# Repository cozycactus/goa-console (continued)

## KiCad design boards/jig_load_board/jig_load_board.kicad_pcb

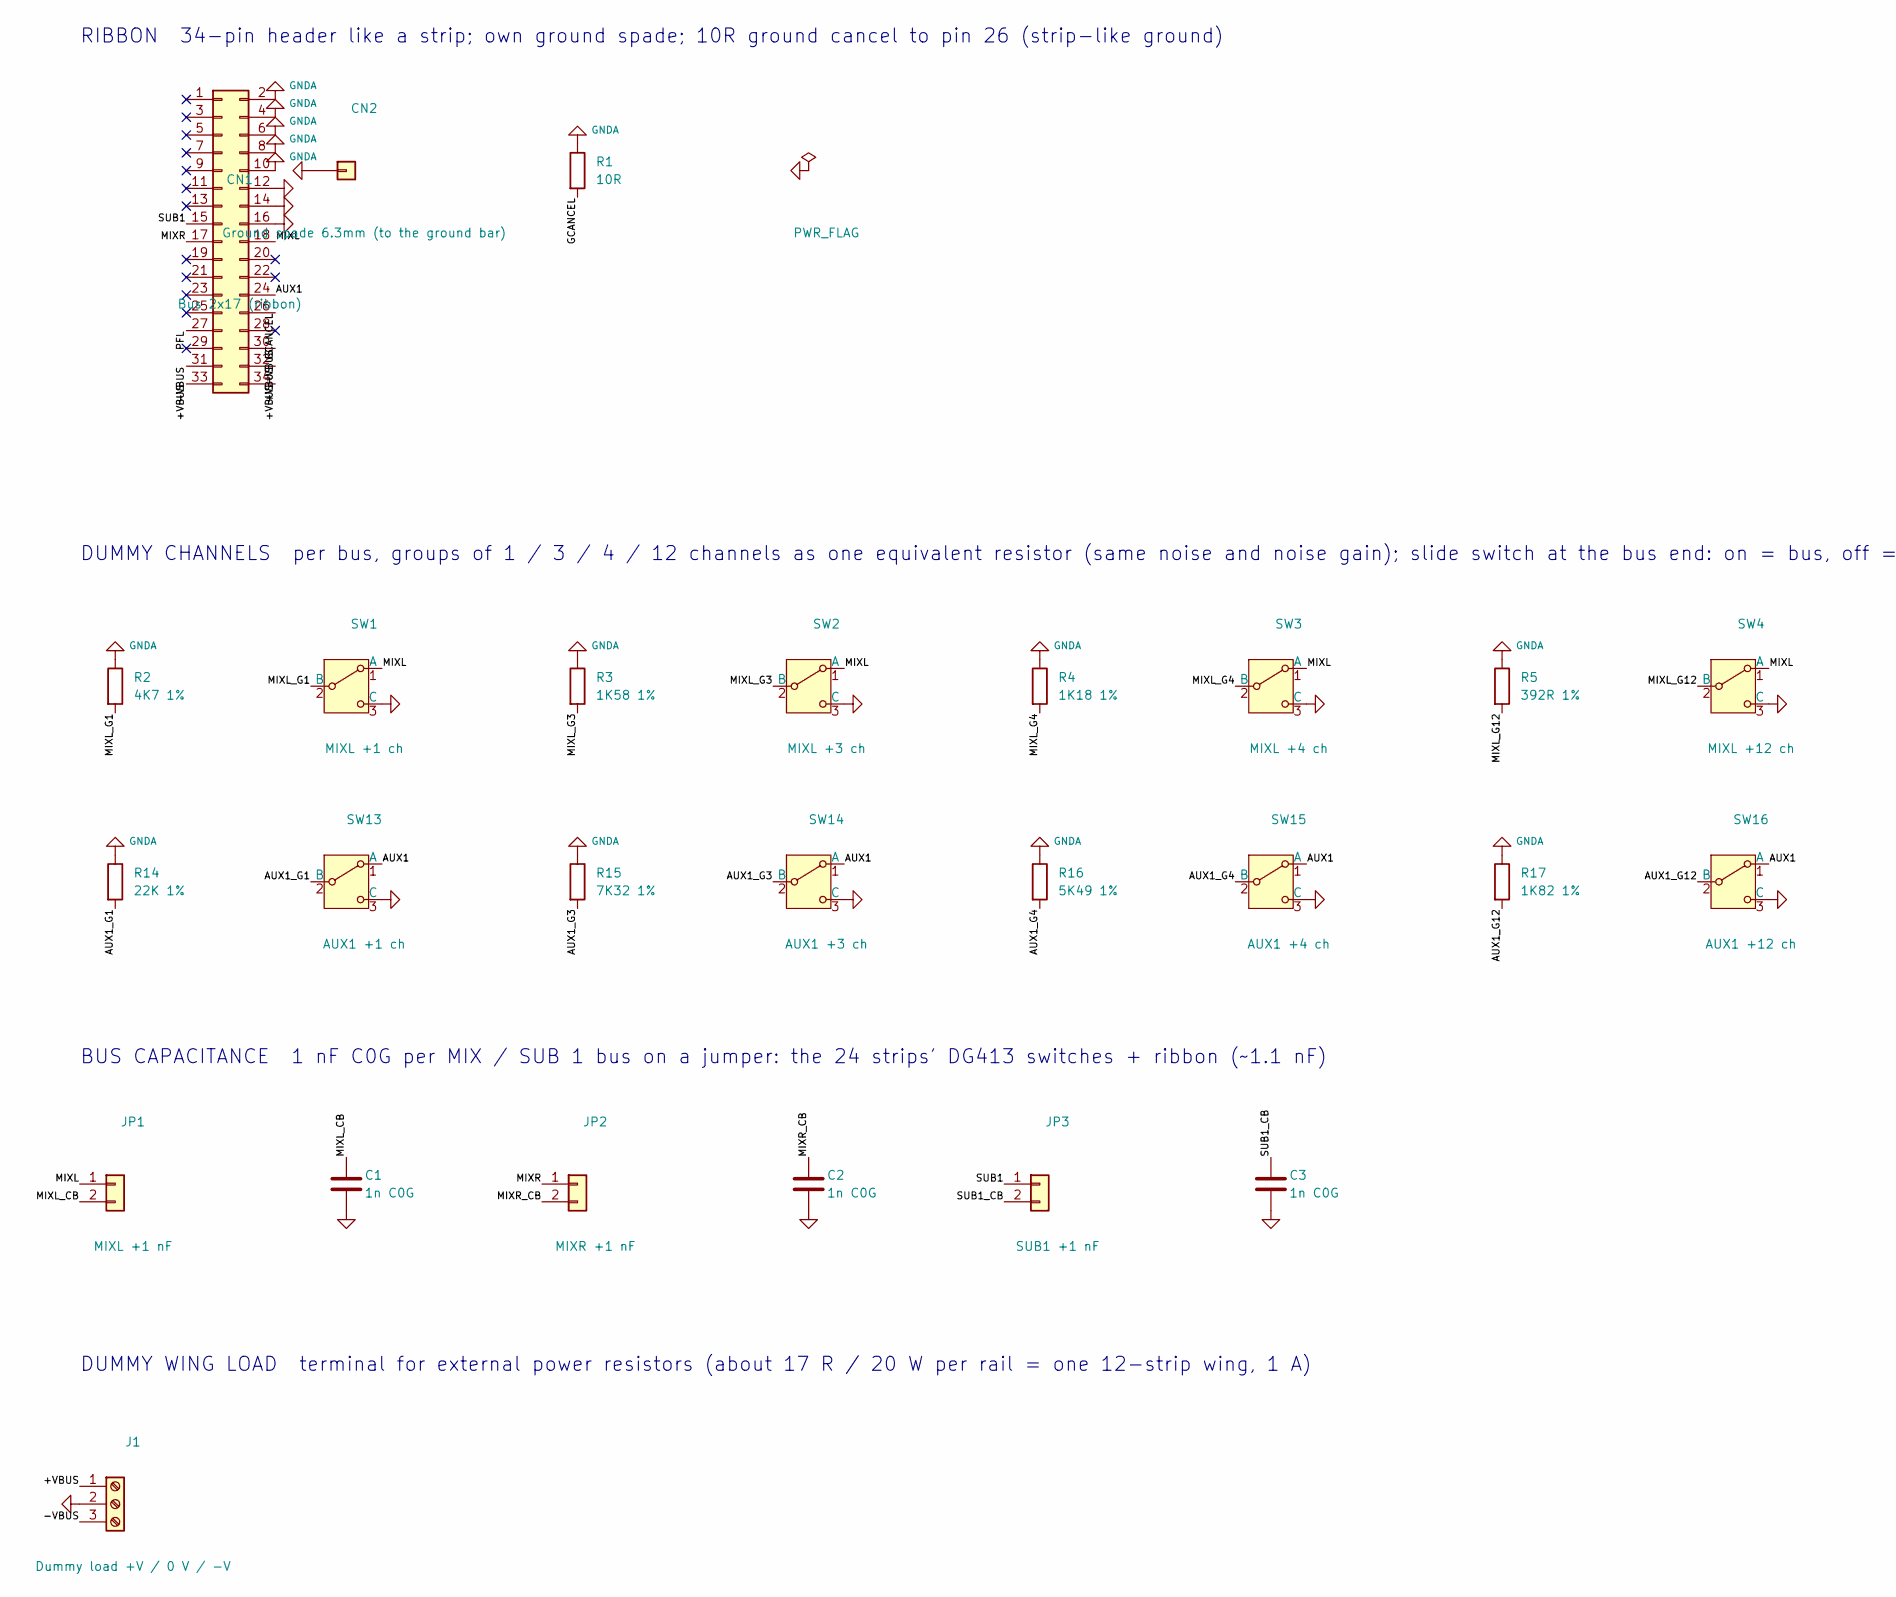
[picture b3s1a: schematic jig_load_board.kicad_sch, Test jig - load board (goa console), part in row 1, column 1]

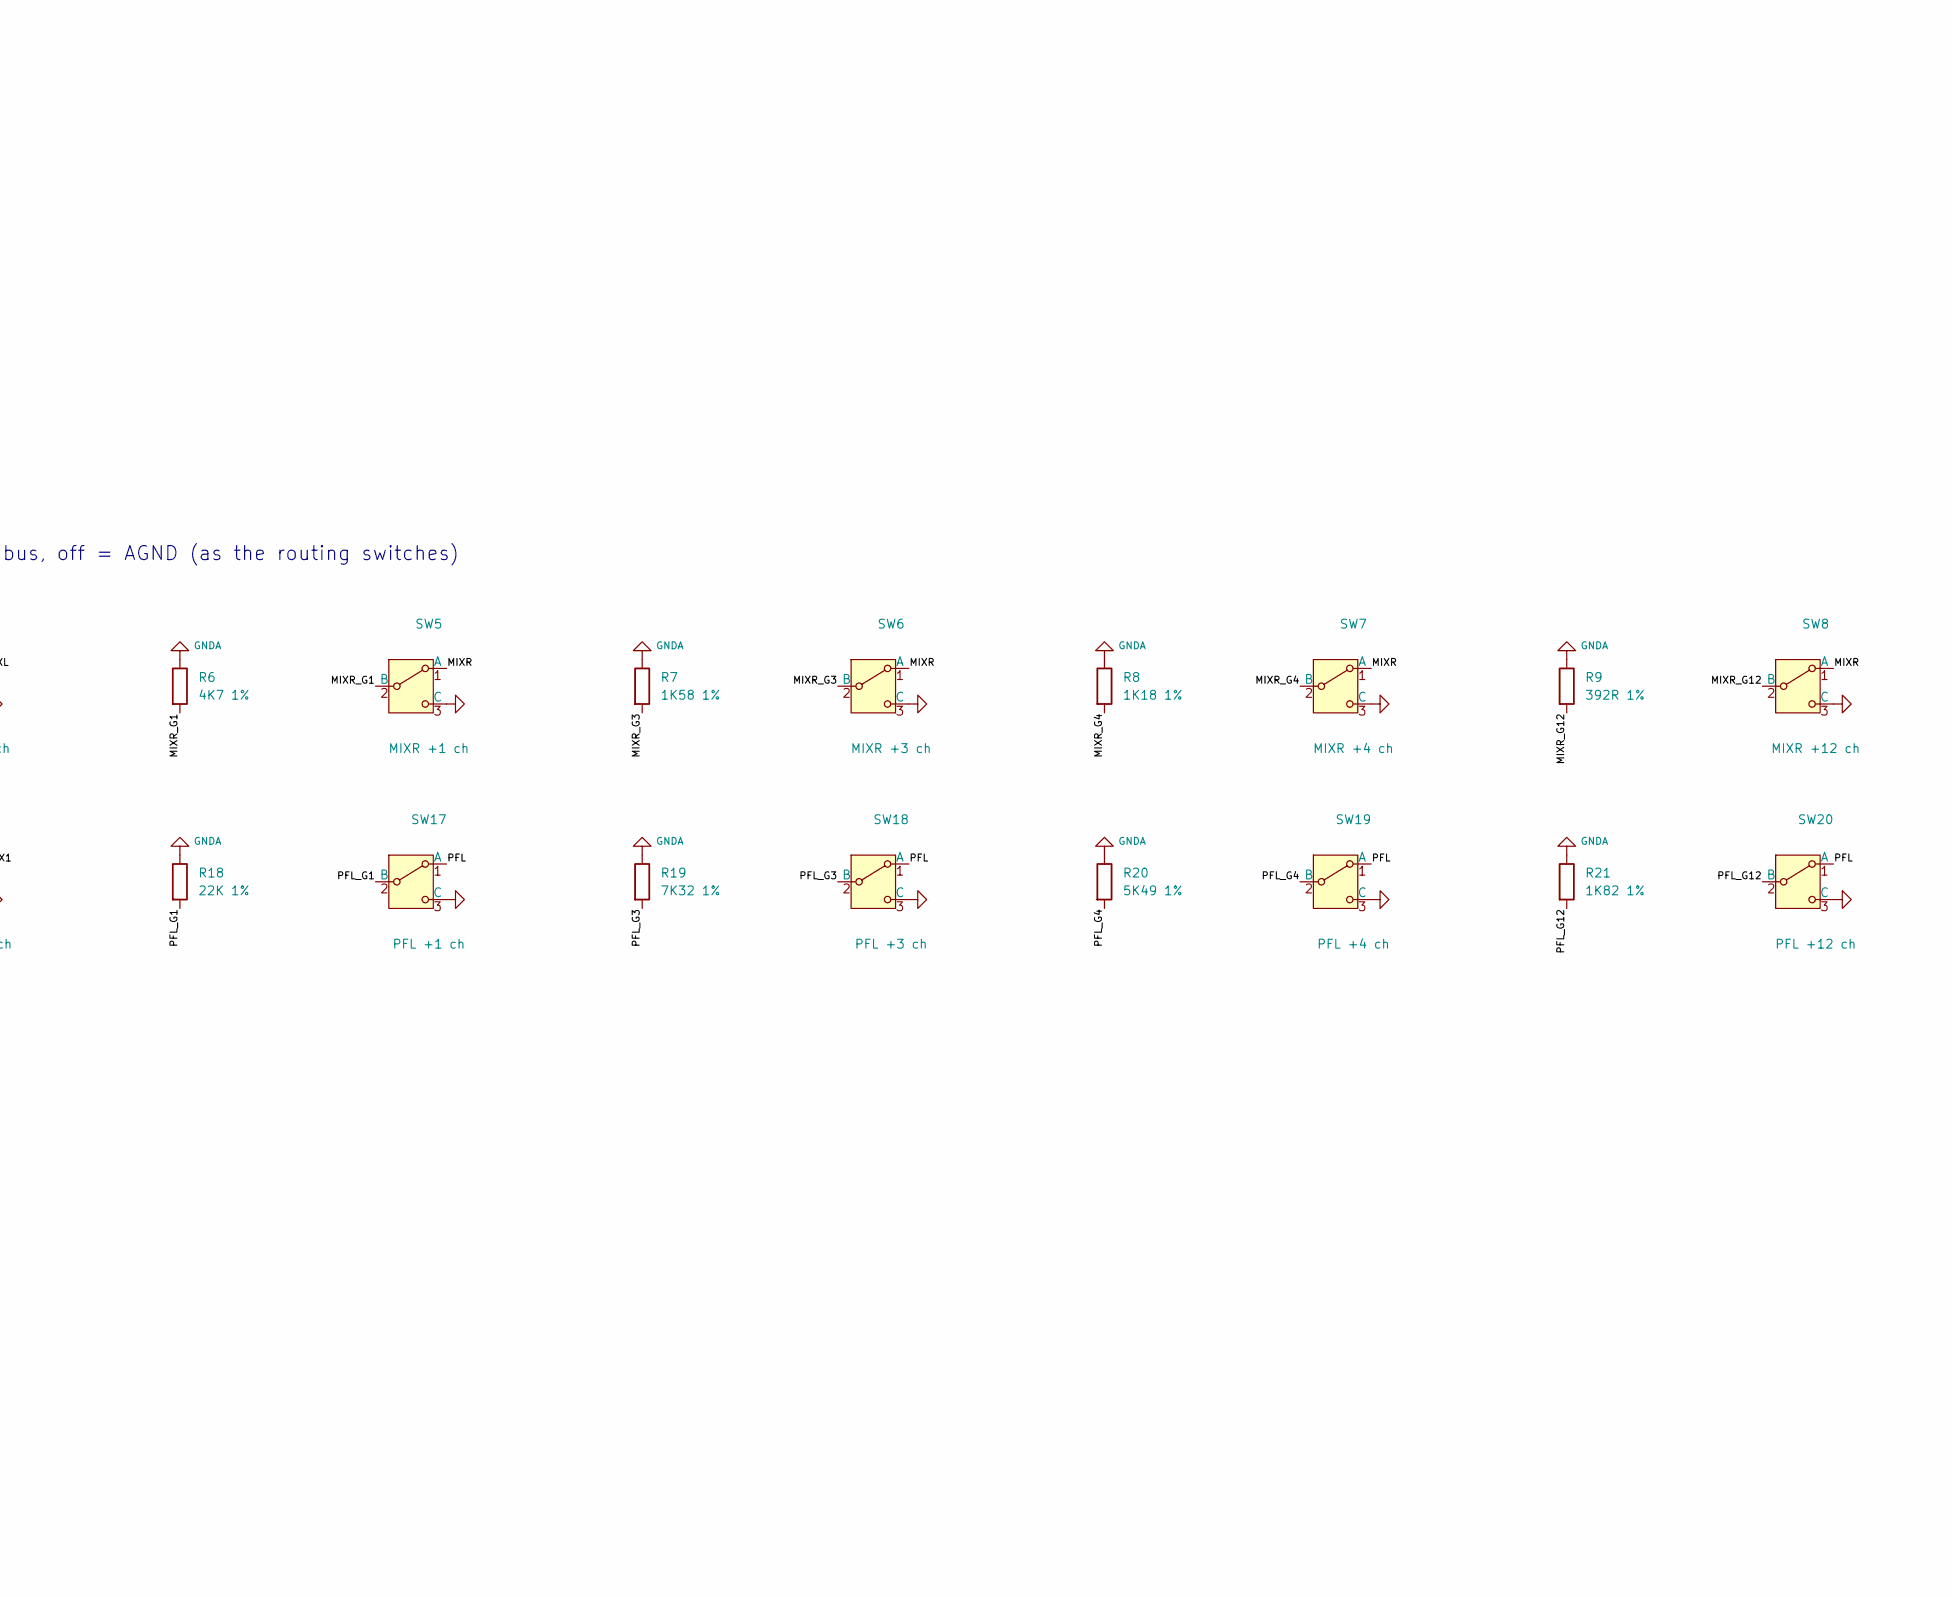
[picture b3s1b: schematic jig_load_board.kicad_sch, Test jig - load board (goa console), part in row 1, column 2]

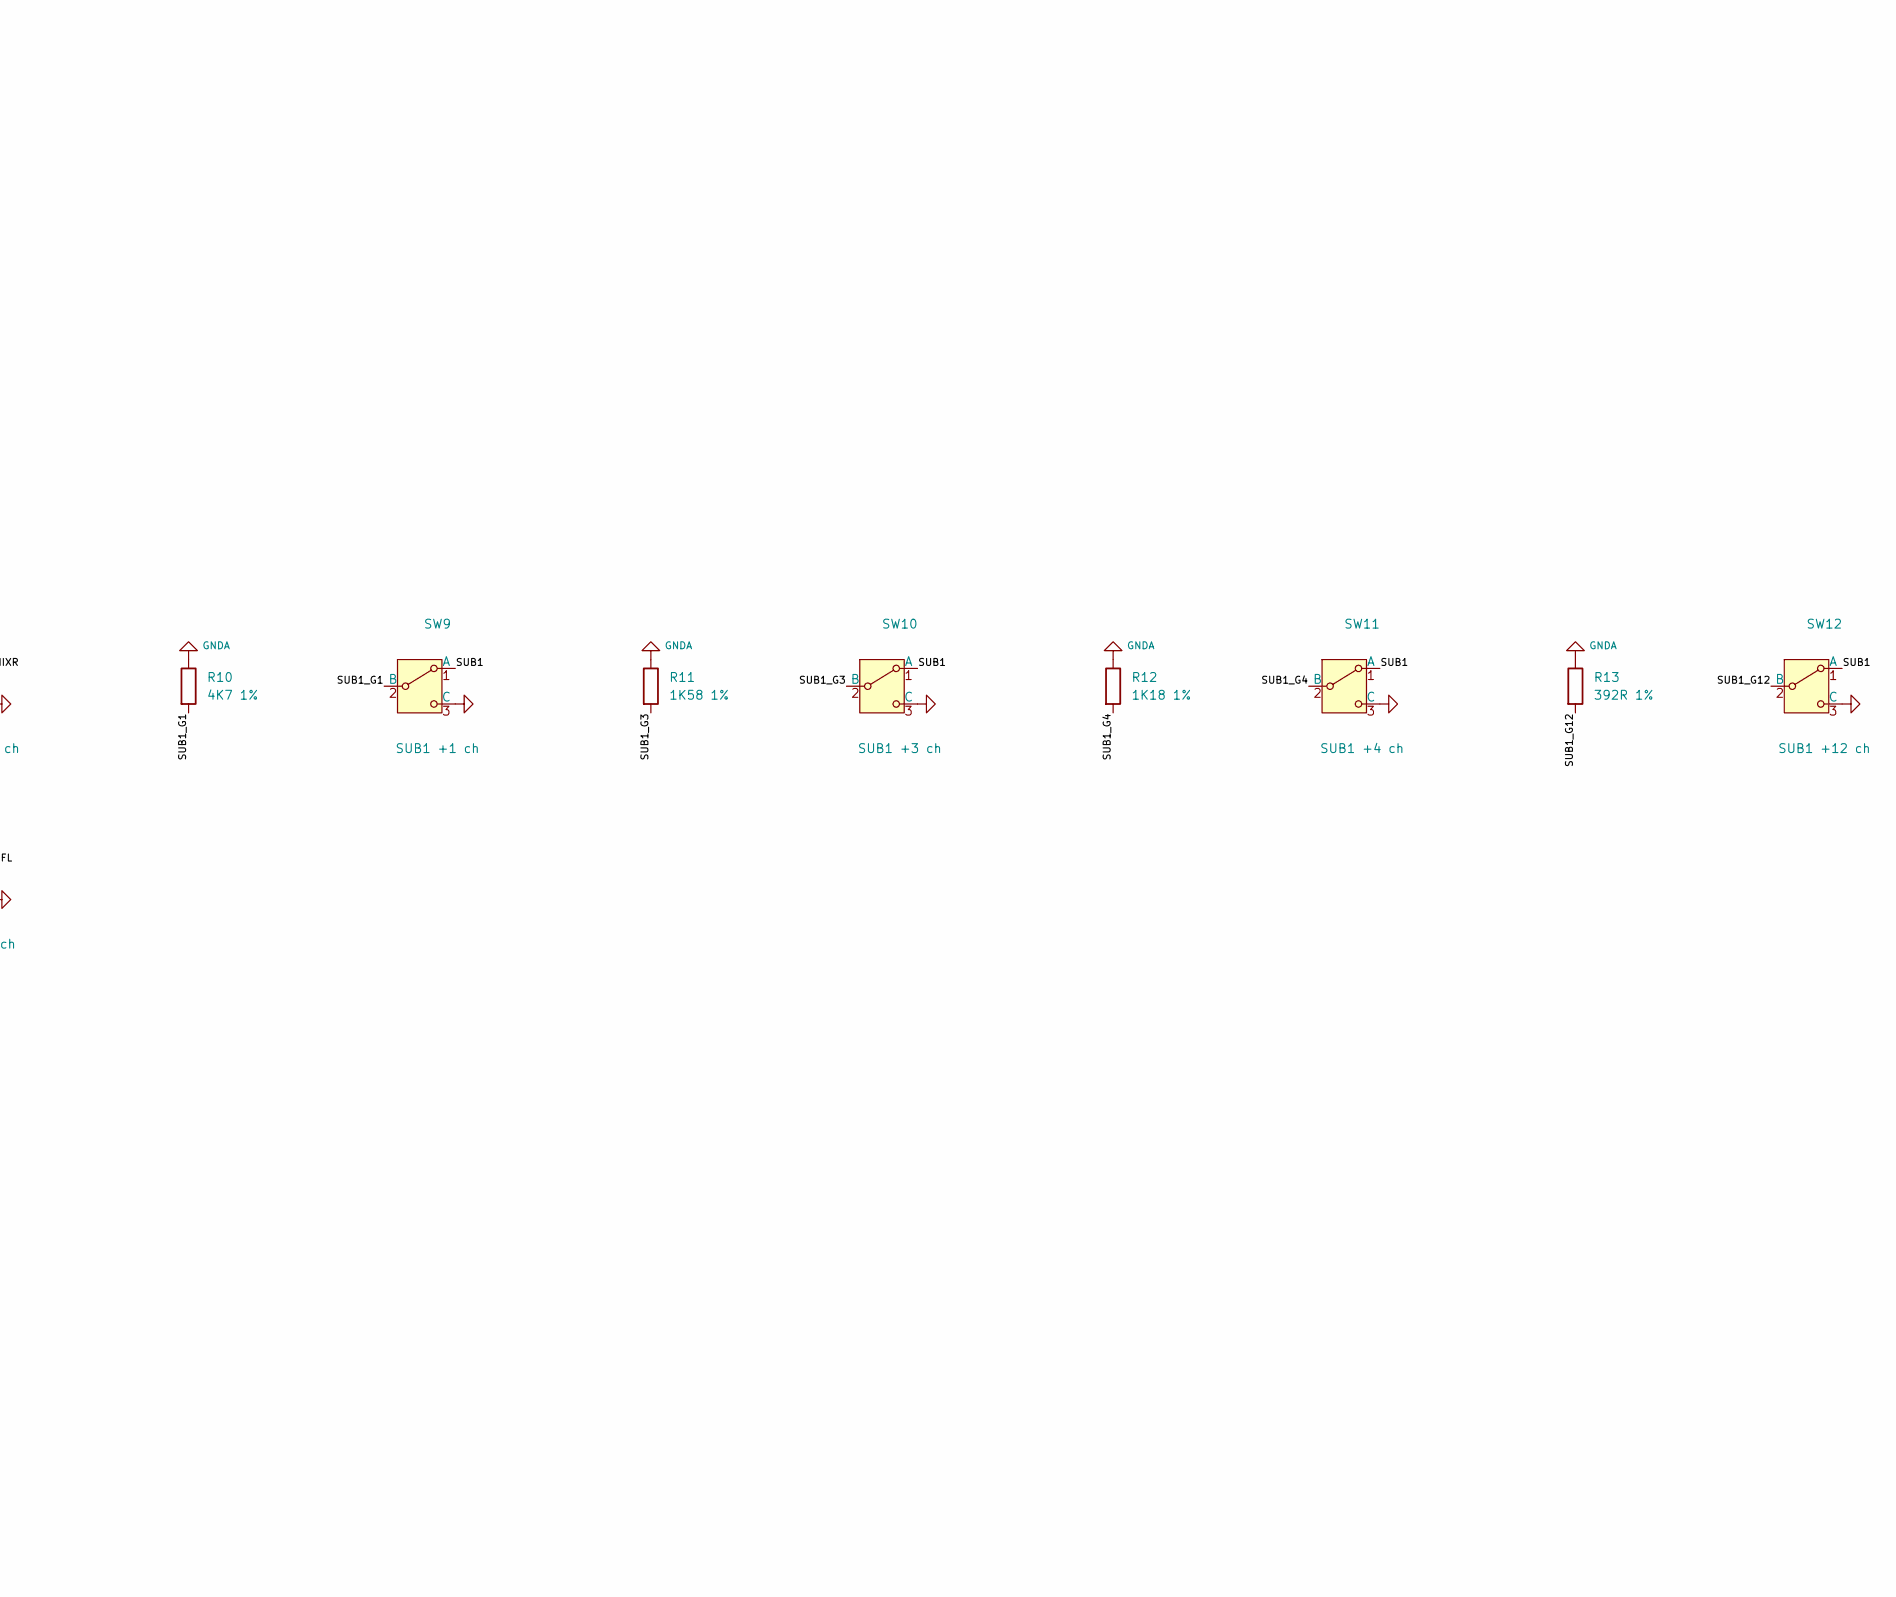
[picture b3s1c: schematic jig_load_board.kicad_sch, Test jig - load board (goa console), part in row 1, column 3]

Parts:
C1, C2, C3: 1n C0G; C_0805_2012Metric; MPN KEMET C0805C102J5GACTU
CN1: Bus 2x17 (ribbon); IDC-Header_2x17_P2.54mm_Vertical; MPN Wurth 61203421621 (2x17 box header)
CN2: Ground spade 6.3mm (to the ground bar); Keystone_1287-ST_FastOn_Tab_6.35mm; MPN Keystone 1287-ST
J1: Dummy load +V / 0 V / -V; TerminalBlock_Phoenix_MKDS-1,5-3-5.08_1x03_P5.08mm_Horizont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; MPN Phoenix 1715734 MKDS 1,5/3-5,08
JP1: MIXL +1 nF; PinHeader_1x02_P2.54mm_Vertical; MPN 2.54 mm header + shunt
JP2: MIXR +1 nF; PinHeader_1x02_P2.54mm_Vertical; MPN 2.54 mm header + shunt
JP3: SUB1 +1 nF; PinHeader_1x02_P2.54mm_Vertical; MPN 2.54 mm header + shunt
R1: 10R; R_0805_2012Metric
R2, R6, R10: 4K7 1%; R_0805_2012Metric
R3, R7, R11: 1K58 1%; R_0805_2012Metric
R4, R8, R12: 1K18 1%; R_0805_2012Metric
R5, R9, R13: 392R 1%; R_0805_2012Metric
R14, R18: 22K 1%; R_0805_2012Metric
R15, R19: 7K32 1%; R_0805_2012Metric
R16, R20: 5K49 1%; R_0805_2012Metric
R17, R21: 1K82 1%; R_0805_2012Metric
SW1: MIXL +1 ch; SW_Slide_SPDT_Straight_CK_OS102011MS2Q; MPN C&K OS102011MS2QN1
SW2: MIXL +3 ch; SW_Slide_SPDT_Straight_CK_OS102011MS2Q; MPN C&K OS102011MS2QN1
SW3: MIXL +4 ch; SW_Slide_SPDT_Straight_CK_OS102011MS2Q; MPN C&K OS102011MS2QN1
SW4: MIXL +12 ch; SW_Slide_SPDT_Straight_CK_OS102011MS2Q; MPN C&K OS102011MS2QN1
SW5: MIXR +1 ch; SW_Slide_SPDT_Straight_CK_OS102011MS2Q; MPN C&K OS102011MS2QN1
SW6: MIXR +3 ch; SW_Slide_SPDT_Straight_CK_OS102011MS2Q; MPN C&K OS102011MS2QN1
SW7: MIXR +4 ch; SW_Slide_SPDT_Straight_CK_OS102011MS2Q; MPN C&K OS102011MS2QN1
SW8: MIXR +12 ch; SW_Slide_SPDT_Straight_CK_OS102011MS2Q; MPN C&K OS102011MS2QN1
SW9: SUB1 +1 ch; SW_Slide_SPDT_Straight_CK_OS102011MS2Q; MPN C&K OS102011MS2QN1
SW10: SUB1 +3 ch; SW_Slide_SPDT_Straight_CK_OS102011MS2Q; MPN C&K OS102011MS2QN1
SW11: SUB1 +4 ch; SW_Slide_SPDT_Straight_CK_OS102011MS2Q; MPN C&K OS102011MS2QN1
SW12: SUB1 +12 ch; SW_Slide_SPDT_Straight_CK_OS102011MS2Q; MPN C&K OS102011MS2QN1
SW13: AUX1 +1 ch; SW_Slide_SPDT_Straight_CK_OS102011MS2Q; MPN C&K OS102011MS2QN1
SW14: AUX1 +3 ch; SW_Slide_SPDT_Straight_CK_OS102011MS2Q; MPN C&K OS102011MS2QN1
SW15: AUX1 +4 ch; SW_Slide_SPDT_Straight_CK_OS102011MS2Q; MPN C&K OS102011MS2QN1
SW16: AUX1 +12 ch; SW_Slide_SPDT_Straight_CK_OS102011MS2Q; MPN C&K OS102011MS2QN1
SW17: PFL +1 ch; SW_Slide_SPDT_Straight_CK_OS102011MS2Q; MPN C&K OS102011MS2QN1
SW18: PFL +3 ch; SW_Slide_SPDT_Straight_CK_OS102011MS2Q; MPN C&K OS102011MS2QN1
SW19: PFL +4 ch; SW_Slide_SPDT_Straight_CK_OS102011MS2Q; MPN C&K OS102011MS2QN1
SW20: PFL +12 ch; SW_Slide_SPDT_Straight_CK_OS102011MS2Q; MPN C&K OS102011MS2QN1

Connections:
/+VBUS: CN1.32, CN1.33, CN1.34, J1.1
/-VBUS: CN1.30, CN1.31, J1.3
/AUX1: CN1.24, SW13.1 (A), SW14.1 (A), SW15.1 (A), SW16.1 (A)
/AUX1_G1: R14.2, SW13.2 (B)
/AUX1_G3: R15.2, SW14.2 (B)
/AUX1_G4: R16.2, SW15.2 (B)
/AUX1_G12: R17.2, SW16.2 (B)
/GCANCEL: CN1.26, R1.2
/MIXL: CN1.18, JP1.1, SW1.1 (A), SW2.1 (A), SW3.1 (A), SW4.1 (A)
/MIXL_CB: C1.1, JP1.2
/MIXL_G1: R2.2, SW1.2 (B)
/MIXL_G3: R3.2, SW2.2 (B)
/MIXL_G4: R4.2, SW3.2 (B)
/MIXL_G12: R5.2, SW4.2 (B)
/MIXR: CN1.17, JP2.1, SW5.1 (A), SW6.1 (A), SW7.1 (A), SW8.1 (A)
/MIXR_CB: C2.1, JP2.2
/MIXR_G1: R6.2, SW5.2 (B)
/MIXR_G3: R7.2, SW6.2 (B)
/MIXR_G4: R8.2, SW7.2 (B)
/MIXR_G12: R9.2, SW8.2 (B)
/PFL: CN1.27, SW17.1 (A), SW18.1 (A), SW19.1 (A), SW20.1 (A)
/PFL_G1: R18.2, SW17.2 (B)
/PFL_G3: R19.2, SW18.2 (B)
/PFL_G4: R20.2, SW19.2 (B)
/PFL_G12: R21.2, SW20.2 (B)
/SUB1: CN1.15, JP3.1, SW9.1 (A), SW10.1 (A), SW11.1 (A), SW12.1 (A)
/SUB1_CB: C3.1, JP3.2
/SUB1_G1: R10.2, SW9.2 (B)
/SUB1_G3: R11.2, SW10.2 (B)
/SUB1_G4: R12.2, SW11.2 (B)
/SUB1_G12: R13.2, SW12.2 (B)
GNDA: C1.2, C2.2, C3.2, CN1.2, CN1.4, CN1.6, CN1.8, CN1.10, CN1.12, CN1.14, CN1.16, CN2.1, J1.2, R1.1, R2.1, R3.1, R4.1, R5.1, R6.1, R7.1, R8.1, R9.1, R10.1, R11.1, R12.1, R13.1, R14.1, R15.1, R16.1, R17.1, R18.1, R19.1, R20.1, R21.1, SW1.3 (C), SW2.3 (C), SW3.3 (C), SW4.3 (C), SW5.3 (C), SW6.3 (C), SW7.3 (C), SW8.3 (C), SW9.3 (C), SW10.3 (C), SW11.3 (C), SW12.3 (C), SW13.3 (C), SW14.3 (C), SW15.3 (C), SW16.3 (C), SW17.3 (C), SW18.3 (C), SW19.3 (C), SW20.3 (C)

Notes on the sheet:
RIBBON 34-pin header like a strip; own ground spade; 10R ground cancel to pin 26 (strip-like ground)
DUMMY CHANNELS per bus, groups of 1 / 3 / 4 / 12 channels as one equivalent resistor (same noise and noise gain); slide switch at the bus end: on = bus, off = AGND (as the routing switches)
BUS CAPACITANCE 1 nF C0G per MIX / SUB 1 bus on a jumper: the 24 strips' DG413 switches + ribbon (~1.1 nF)
DUMMY WING LOAD terminal for external power resistors (about 17 R / 20 W per rail = one 12-strip wing, 1 A)

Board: 2 copper layers, 54 parts (0 on the bottom side), 32 nets, no tracks yet.

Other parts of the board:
H1, H2, H3, H4: M3 standoff; MountingHole_3.2mm_M3

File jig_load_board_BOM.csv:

"Qty","Value","Footprint","MPN","DNP","References"
"3","1n C0G","Capacitor_SMD:C_0805_2012Metric","KEMET C0805C102J5GACTU","","C1 C2 C3"
"1","Bus 2x17 (ribbon)","Connector_IDC:IDC-Header_2x17_P2.54mm_Vertical","Wurth 61203421621 (2x17 box header)","","CN1"
"1","Ground spade 6.3mm (to the ground bar)","goa-console:Keystone_1287-ST_FastOn_Tab_6.35mm","Keystone 1287-ST","","CN2"
"1","Dummy load +V / 0 V / -V","TerminalBlock_Phoenix:TerminalBlock_Phoenix_MKDS-1,5-3-5.08_1x03_P5.08mm_Horizontal","Phoenix MKDS 1,5/3-5,08","","J1"
"1","MIXL +1 nF","Connector_PinHeader_2.54mm:PinHeader_1x02_P2.54mm_Vertical","2.54 mm header + shunt","","JP1"
"1","MIXR +1 nF","Connector_PinHeader_2.54mm:PinHeader_1x02_P2.54mm_Vertical","2.54 mm header + shunt","","JP2"
"1","SUB1 +1 nF","Connector_PinHeader_2.54mm:PinHeader_1x02_P2.54mm_Vertical","2.54 mm header + shunt","","JP3"
"1","10R","Resistor_SMD:R_0805_2012Metric","","","R1"
"3","4K7 1%","Resistor_SMD:R_0805_2012Metric","","","R2 R6 R10"
"3","1K58 1%","Resistor_SMD:R_0805_2012Metric","","","R3 R7 R11"
"3","1K18 1%","Resistor_SMD:R_0805_2012Metric","","","R4 R8 R12"
"3","392R 1%","Resistor_SMD:R_0805_2012Metric","","","R5 R9 R13"
"2","22K 1%","Resistor_SMD:R_0805_2012Metric","","","R14 R18"
"2","7K32 1%","Resistor_SMD:R_0805_2012Metric","","","R15 R19"
"2","5K49 1%","Resistor_SMD:R_0805_2012Metric","","","R16 R20"
"2","1K82 1%","Resistor_SMD:R_0805_2012Metric","","","R17 R21"
"1","MIXL +1 ch","Button_Switch_THT:SW_Slide_SPDT_Straight_CK_OS102011MS2Q","C&K OS102011MS2QN1","","SW1"
"1","MIXL +3 ch","Button_Switch_THT:SW_Slide_SPDT_Straight_CK_OS102011MS2Q","C&K OS102011MS2QN1","","SW2"
"1","MIXL +4 ch","Button_Switch_THT:SW_Slide_SPDT_Straight_CK_OS102011MS2Q","C&K OS102011MS2QN1","","SW3"
"1","MIXL +12 ch","Button_Switch_THT:SW_Slide_SPDT_Straight_CK_OS102011MS2Q","C&K OS102011MS2QN1","","SW4"
"1","MIXR +1 ch","Button_Switch_THT:SW_Slide_SPDT_Straight_CK_OS102011MS2Q","C&K OS102011MS2QN1","","SW5"
"1","MIXR +3 ch","Button_Switch_THT:SW_Slide_SPDT_Straight_CK_OS102011MS2Q","C&K OS102011MS2QN1","","SW6"
"1","MIXR +4 ch","Button_Switch_THT:SW_Slide_SPDT_Straight_CK_OS102011MS2Q","C&K OS102011MS2QN1","","SW7"
"1","MIXR +12 ch","Button_Switch_THT:SW_Slide_SPDT_Straight_CK_OS102011MS2Q","C&K OS102011MS2QN1","","SW8"
"1","SUB1 +1 ch","Button_Switch_THT:SW_Slide_SPDT_Straight_CK_OS102011MS2Q","C&K OS102011MS2QN1","","SW9"
"1","SUB1 +3 ch","Button_Switch_THT:SW_Slide_SPDT_Straight_CK_OS102011MS2Q","C&K OS102011MS2QN1","","SW10"
"1","SUB1 +4 ch","Button_Switch_THT:SW_Slide_SPDT_Straight_CK_OS102011MS2Q","C&K OS102011MS2QN1","","SW11"
"1","SUB1 +12 ch","Button_Switch_THT:SW_Slide_SPDT_Straight_CK_OS102011MS2Q","C&K OS102011MS2QN1","","SW12"
"1","AUX1 +1 ch","Button_Switch_THT:SW_Slide_SPDT_Straight_CK_OS102011MS2Q","C&K OS102011MS2QN1","","SW13"
"1","AUX1 +3 ch","Button_Switch_THT:SW_Slide_SPDT_Straight_CK_OS102011MS2Q","C&K OS102011MS2QN1","","SW14"
"1","AUX1 +4 ch","Button_Switch_THT:SW_Slide_SPDT_Straight_CK_OS102011MS2Q","C&K OS102011MS2QN1","","SW15"
"1","AUX1 +12 ch","Button_Switch_THT:SW_Slide_SPDT_Straight_CK_OS102011MS2Q","C&K OS102011MS2QN1","","SW16"
"1","PFL +1 ch","Button_Switch_THT:SW_Slide_SPDT_Straight_CK_OS102011MS2Q","C&K OS102011MS2QN1","","SW17"
"1","PFL +3 ch","Button_Switch_THT:SW_Slide_SPDT_Straight_CK_OS102011MS2Q","C&K OS102011MS2QN1","","SW18"
"1","PFL +4 ch","Button_Switch_THT:SW_Slide_SPDT_Straight_CK_OS102011MS2Q","C&K OS102011MS2QN1","","SW19"
"1","PFL +12 ch","Button_Switch_THT:SW_Slide_SPDT_Straight_CK_OS102011MS2Q","C&K OS102011MS2QN1","","SW20"

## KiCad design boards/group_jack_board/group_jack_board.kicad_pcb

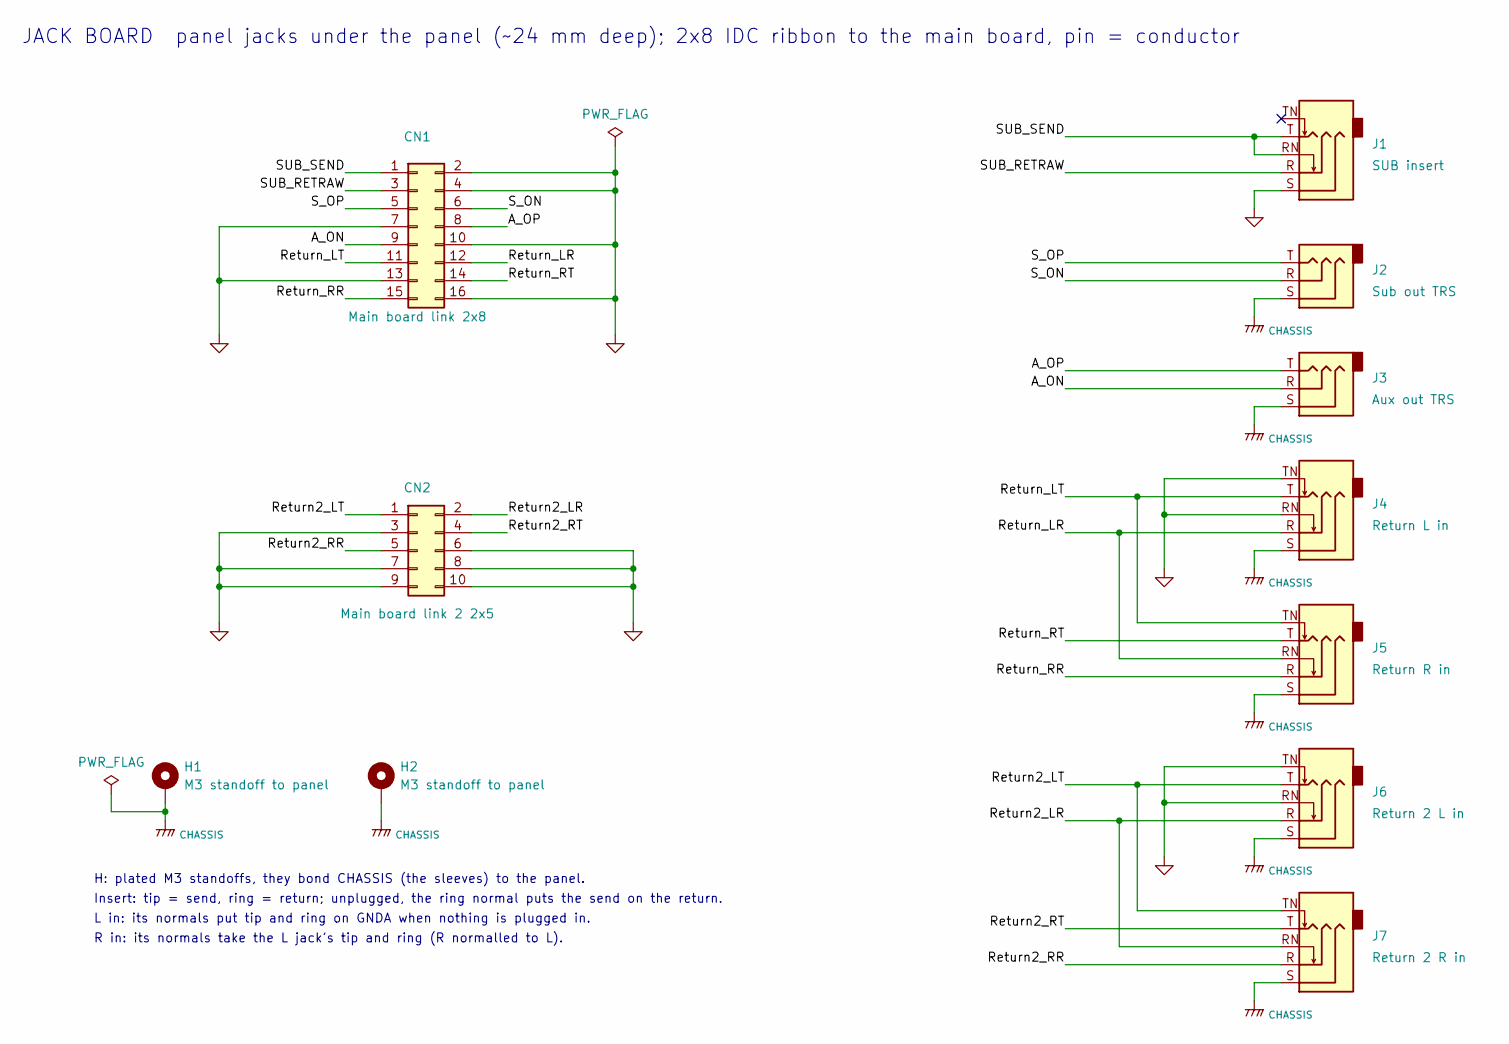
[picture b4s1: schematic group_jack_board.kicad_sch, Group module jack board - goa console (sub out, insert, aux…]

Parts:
CN1: Main board link 2x8; IDC-Header_2x08_P2.54mm_Vertical; MPN Wurth 61201621621 (2x8 box header)
CN2: Main board link 2 2x5; IDC-Header_2x05_P2.54mm_Vertical; MPN Wurth 61201021621 (2x5 box header)
H1, H2: M3 standoff to panel; MountingHole_3.2mm_M3_Pad
J1: SUB insert; Jack_6.35mm_Neutrik_NJ6FD-V_Vertical; MPN Neutrik NJ6FD-V
J2: Sub out TRS; Jack_6.35mm_Neutrik_NJ6FD-V_Vertical; MPN Neutrik NJ6FD-V
J3: Aux out TRS; Jack_6.35mm_Neutrik_NJ6FD-V_Vertical; MPN Neutrik NJ6FD-V
J4: Return L in; Jack_6.35mm_Neutrik_NJ6FD-V_Vertical; MPN Neutrik NJ6FD-V
J5: Return R in; Jack_6.35mm_Neutrik_NJ6FD-V_Vertical; MPN Neutrik NJ6FD-V
J6: Return 2 L in; Jack_6.35mm_Neutrik_NJ6FD-V_Vertical; MPN Neutrik NJ6FD-V
J7: Return 2 R in; Jack_6.35mm_Neutrik_NJ6FD-V_Vertical; MPN Neutrik NJ6FD-V

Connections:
/A_ON: CN1.9, J3.R
/A_OP: CN1.8, J3.T
/CHASSIS: H1.1, H2.1, J2.S, J3.S, J4.S, J5.S, J6.S, J7.S
/Return2_LR: CN2.2, J6.R, J7.RN
/Return2_LT: CN2.1, J6.T, J7.TN
/Return2_RR: CN2.5, J7.R
/Return2_RT: CN2.4, J7.T
/Return_LR: CN1.12, J4.R, J5.RN
/Return_LT: CN1.11, J4.T, J5.TN
/Return_RR: CN1.15, J5.R
/Return_RT: CN1.14, J5.T
/SUB_RETRAW: CN1.3, J1.R
/SUB_SEND: CN1.1, J1.RN, J1.T
/S_ON: CN1.6, J2.R
/S_OP: CN1.5, J2.T
GNDA: CN1.2, CN1.4, CN1.7, CN1.10, CN1.13, CN1.16, CN2.3, CN2.6, CN2.7, CN2.8, CN2.9, CN2.10, J1.S, J4.RN, J4.TN, J6.RN, J6.TN

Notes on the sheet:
JACK BOARD panel jacks under the panel (~24 mm deep); 2x8 IDC ribbon to the main board, pin = conductor
H: plated M3 standoffs, they bond CHASSIS (the sleeves) to the panel.
Insert: tip = send, ring = return; unplugged, the ring normal puts the send on the return.
L in: its normals put tip and ring on GNDA when nothing is plugged in.
R in: its normals take the L jack's tip and ring (R normalled to L).

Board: 2 copper layers, 11 parts (2 on the bottom side), 16 nets, no tracks yet.

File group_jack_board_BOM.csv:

"Qty","Value","Footprint","MPN","DNP","References"
"1","Main board link 2x8","Connector_IDC:IDC-Header_2x08_P2.54mm_Vertical","Wurth 61201621621 (2x8 box header)","","CN1"
"1","Main board link 2 2x5","Connector_IDC:IDC-Header_2x05_P2.54mm_Vertical","Wurth 61201021621 (2x5 box header)","","CN2"
"1","SUB insert","Connector_Audio:Jack_6.35mm_Neutrik_NJ6FD-V_Vertical","Neutrik NJ6FD-V","","J1"
"1","Sub out TRS","Connector_Audio:Jack_6.35mm_Neutrik_NJ6FD-V_Vertical","Neutrik NJ6FD-V","","J2"
"1","Aux out TRS","Connector_Audio:Jack_6.35mm_Neutrik_NJ6FD-V_Vertical","Neutrik NJ6FD-V","","J3"
"1","Return L in","Connector_Audio:Jack_6.35mm_Neutrik_NJ6FD-V_Vertical","Neutrik NJ6FD-V","","J4"
"1","Return R in","Connector_Audio:Jack_6.35mm_Neutrik_NJ6FD-V_Vertical","Neutrik NJ6FD-V","","J5"
"1","Return 2 L in","Connector_Audio:Jack_6.35mm_Neutrik_NJ6FD-V_Vertical","Neutrik NJ6FD-V","","J6"
"1","Return 2 R in","Connector_Audio:Jack_6.35mm_Neutrik_NJ6FD-V_Vertical","Neutrik NJ6FD-V","","J7"
